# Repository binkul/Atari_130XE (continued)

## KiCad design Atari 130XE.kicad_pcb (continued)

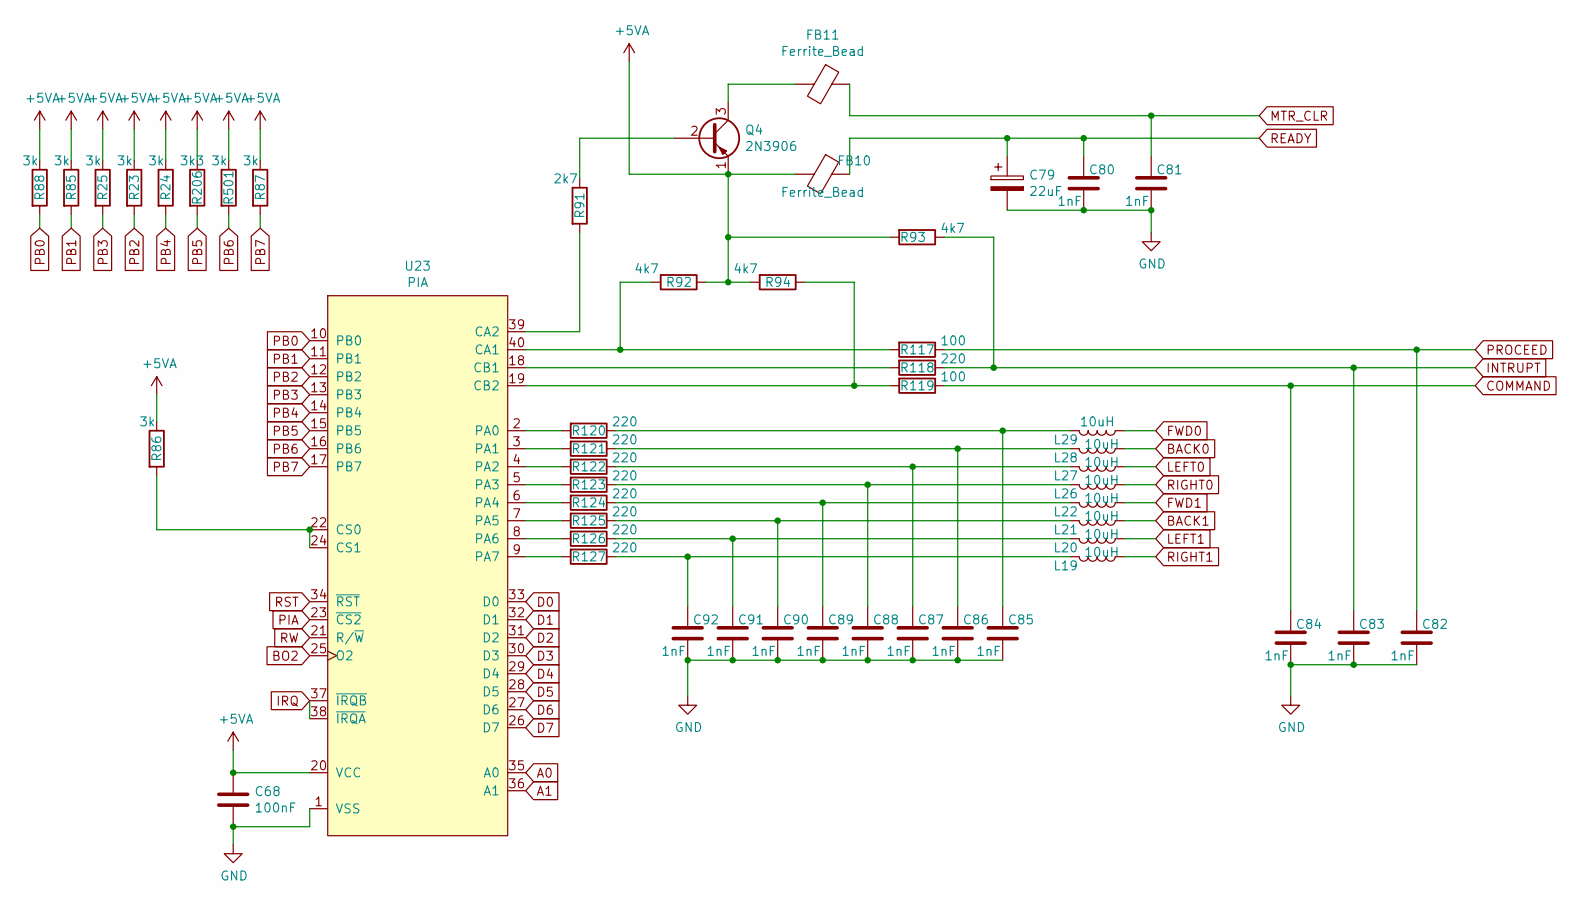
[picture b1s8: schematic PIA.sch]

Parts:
C68: 100nF; C_Axial_L5.1mm_D2.5mm_P12.50mm_Horizontal
C79: 22uF; CP_Axial_L11.0mm_D5.0mm_P18.00mm_Horizontal
C80, C81, C82, C83, C84, C85, C86, C87, C88, C89, C90, C91, C92: 1nF; C_Axial_L5.1mm_D2.5mm_P12.50mm_Horizontal
FB10, FB11: Ferrite_Bead; L_Axial_L7.0mm_D3.3mm_P12.50mm_Horizontal_Fastron_MICC
L19, L20, L21, L22, L26, L27, L28, L29: 10uH; L_Axial_L7.0mm_D3.3mm_P12.50mm_Horizontal_Fastron_MICC
Q4: 2N3906; TO-92_Wide
R23, R24, R25, R85, R86, R87, R88, R501: 3k; R_Axial_DIN0207_L3.6mm_D2.2mm_P10.16mm_Horizontal
R91: 2k7; R_Axial_DIN0207_L3.6mm_D2.2mm_P10.16mm_Horizontal
R92, R93, R94: 4k7; R_Axial_DIN0207_L3.6mm_D2.2mm_P10.16mm_Horizontal
R117, R119: 100; R_Axial_DIN0207_L3.6mm_D2.2mm_P10.16mm_Horizontal
R118, R120, R121, R122, R123, R124, R125, R126, R127: 220; R_Axial_DIN0207_L3.6mm_D2.2mm_P10.16mm_Horizontal
R206: 3k3; R_Axial_DIN0207_L3.6mm_D2.2mm_P10.16mm_Horizontal
U23: PIA; DIP-40_W15.24mm_Socket

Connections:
+5VA: C68.1, FB10.2, Q4.1 (E), R23.1, R24.1, R25.1, R85.1, R86.1, R87.1, R88.1, R92.1, R93.2, R94.2, R206.1, R501.1, U23.20 (VCC); also elsewhere on the board
A0: U23.35 (A0); also elsewhere on the board
A1: U23.36 (A1); also elsewhere on the board
BACK0: L28.1; also elsewhere on the board
BACK1: L21.1; also elsewhere on the board
BO2: U23.25 (O2); also elsewhere on the board
COMMAND: C84.1, R119.1; also elsewhere on the board
D0: U23.33 (D0); also elsewhere on the board
D1: U23.32 (D1); also elsewhere on the board
D2: U23.31 (D2); also elsewhere on the board
D3: U23.30 (D3); also elsewhere on the board
D4: U23.29 (D4); also elsewhere on the board
D5: U23.28 (D5); also elsewhere on the board
D6: U23.27 (D6); also elsewhere on the board
D7: U23.26 (D7); also elsewhere on the board
FWD0: L29.1; also elsewhere on the board
FWD1: L22.1; also elsewhere on the board
GND: C68.2, C79.2, C80.2, C81.2, C82.2, C83.2, C84.2, C85.2, C86.2, C87.2, C88.2, C89.2, C90.2, C91.2, C92.2, U23.1 (VSS); also elsewhere on the board
INTRUPT: C83.1, R93.1, R118.1; also elsewhere on the board
IRQ: U23.37 (~IRQB), U23.38 (~IRQA); also elsewhere on the board
LEFT0: L27.1; also elsewhere on the board
LEFT1: L20.1; also elsewhere on the board
MTR_CLR: C81.1, FB11.1; also elsewhere on the board
unnamed: C85.1, L29.2, R120.1
unnamed: C86.1, L28.2, R121.1
unnamed: C87.1, L27.2, R122.1
unnamed: C88.1, L26.2, R123.1
unnamed: C89.1, L22.2, R124.1
unnamed: C90.1, L21.2, R125.1
unnamed: C91.1, L20.2, R126.1
unnamed: C92.1, L19.2, R127.1
unnamed: FB11.2, Q4.3 (C)
unnamed: Q4.2 (B), R91.1
unnamed: R86.2, U23.22 (CS0), U23.24 (CS1)
unnamed: R91.2, U23.39 (CA2)
unnamed: R92.2, R117.2, U23.40 (CA1)
unnamed: R118.2, U23.18 (CB1)
unnamed: R94.1, R119.2, U23.19 (CB2)
unnamed: R120.2, U23.2 (PA0)
unnamed: R121.2, U23.3 (PA1)
unnamed: R122.2, U23.4 (PA2)
unnamed: R123.2, U23.5 (PA3)
unnamed: R124.2, U23.6 (PA4)
unnamed: R125.2, U23.7 (PA5)
unnamed: R126.2, U23.8 (PA6)
unnamed: R127.2, U23.9 (PA7)
PB0: R88.2, U23.10 (PB0); also elsewhere on the board
PB1: R85.2, U23.11 (PB1); also elsewhere on the board
PB2: R23.2, U23.12 (PB2); also elsewhere on the board
PB3: R25.2, U23.13 (PB3); also elsewhere on the board
PB4: R24.2, U23.14 (PB4); also elsewhere on the board
PB5: R206.2, U23.15 (PB5); also elsewhere on the board
PB6: R501.2, U23.16 (PB6)
PB7: R87.2, U23.17 (PB7); also elsewhere on the board
PIA: U23.23 (~CS2); also elsewhere on the board
PROCEED: C82.1, R117.1; also elsewhere on the board
READY: C79.1, C80.1, FB10.1; also elsewhere on the board
RIGHT0: L26.1; also elsewhere on the board
RIGHT1: L19.1; also elsewhere on the board
RST: U23.34 (~RST); also elsewhere on the board
RW: U23.21 (R/~W); also elsewhere on the board

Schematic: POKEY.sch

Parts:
C62, C71, C72, C73, C74, C75, C76, C77, C78: 1nF; C_Axial_L5.1mm_D2.5mm_P12.50mm_Horizontal
C63, C64, C65, C66: 47nF; C_Axial_L5.1mm_D2.5mm_P12.50mm_Horizontal
C69, C70: 100nF; C_Axial_L5.1mm_D2.5mm_P12.50mm_Horizontal
C98: 10uF; CP_Axial_L11.0mm_D6.0mm_P18.00mm_Horizontal
D5: 1N4148; D_DO-35_SOD27_P12.70mm_Horizontal
J108, J109, J110, J111: pin; PinHeader_1x01_P2.00mm_Vertical
L15, L16, L17, L18: 10uH; L_Axial_L7.0mm_D3.3mm_P12.50mm_Horizontal_Fastron_MICC
R74, R75: 3k; R_Axial_DIN0207_L3.6mm_D2.2mm_P10.16mm_Horizontal
R76, R77, R78, R79: 1k8; R_Axial_DIN0207_L3.6mm_D2.2mm_P10.16mm_Horizontal
R80: 1k; R_Axial_DIN0207_L3.6mm_D2.2mm_P10.16mm_Horizontal
R81, R82, R83, R84: 4k7; R_Axial_DIN0207_L3.6mm_D2.2mm_P10.16mm_Horizontal
R89, R96: 47k; R_Axial_DIN0207_L3.6mm_D2.2mm_P10.16mm_Horizontal
R90, R128, R129, R130, R131: 100; R_Axial_DIN0207_L3.6mm_D2.2mm_P10.16mm_Horizontal
R137: 270; R_Axial_DIN0207_L3.6mm_D2.2mm_P10.16mm_Horizontal
R138, R139, R140, R141, R142, R143, R144, R145, R146, R147, R148, R149, R150, R151, R152, R153: 220; R_Axial_DIN0207_L3.6mm_D2.2mm_P10.16mm_Horizontal
U22: POKEY; DIP-40_W15.24mm_Socket
U24, U25: CD4051B; DIP-16_W7.62mm_Socket
W1: 0; R_Axial_DIN0207_L3.6mm_D2.2mm_P10.16mm_Horizontal

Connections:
+5VA: C69.1, C70.1, D5.1 (K), R74.1, R75.2, R80.2, R81.1, R82.1, R83.1, R84.1, R89.2, R96.2, U24.16 (VDD), U25.16 (VDD); also elsewhere on the board
A0: U22.36 (A0); also elsewhere on the board
A1: U22.35 (A1); also elsewhere on the board
A2: U22.34 (A2); also elsewhere on the board
A3: U22.33 (A3); also elsewhere on the board
BO2: U22.7 (O2); also elsewhere on the board
BSC: R137.1; also elsewhere on the board
CLK_IN: C76.1, R129.1; also elsewhere on the board
CLK_OUT: C75.1, R128.1; also elsewhere on the board
D0: U22.38 (D0); also elsewhere on the board
D1: U22.39 (D1); also elsewhere on the board
D2: U22.40 (D2); also elsewhere on the board
D3: U22.2 (D3); also elsewhere on the board
D4: U22.3 (D4); also elsewhere on the board
D5: U22.4 (D5); also elsewhere on the board
D6: U22.5 (D6); also elsewhere on the board
D7: U22.6 (D7); also elsewhere on the board
DATA_IN: C77.1, R130.1; also elsewhere on the board
DATA_OUT: C78.1, R131.1; also elsewhere on the board
GND: C62.2, C63.2, C64.2, C65.2, C66.2, C69.2, C70.2, C71.2, C72.2, C73.2, C74.2, C75.2, C76.2, C77.2, C78.2, C98.2, J108.1, J109.1, J110.1, J111.1, R90.2, U22.1 (VSS), U22.8 (P6), U22.9 (P7), U22.11 (P5), U24.6 (INH), U24.7 (VEE), U24.8 (VSS), U25.6 (INH), U25.7 (VEE), U25.8 (VSS), W1.2; also elsewhere on the board
IN0: R146.1; also elsewhere on the board
IN1: R147.1; also elsewhere on the board
IN2: R148.1; also elsewhere on the board
IN3: R149.1; also elsewhere on the board
IN4: R150.1; also elsewhere on the board
IN5: R151.1; also elsewhere on the board
IN6: R152.1; also elsewhere on the board
IN7: R153.1; also elsewhere on the board
IRQ: U22.29 (~IRQ); also elsewhere on the board
K0: U22.23 (~K0), U24.11 (A)
K1: U22.22 (~K1), U24.10 (B)
K2: U22.21 (~K2), U24.9 (C)
K3: U22.20 (~K3), U25.11 (A)
K4: U22.19 (~K4), U25.10 (B)
K5: U22.18 (~K5), U25.9 (C)
unnamed: C63.1, R78.2, U22.13 (P3)
unnamed: C64.1, R76.2, U22.15 (P1)
unnamed: C65.1, R77.2, U22.14 (P0)
unnamed: C66.1, R79.2, U22.12 (P2)
unnamed: C71.1, L17.2, R76.1
unnamed: C72.1, L18.2, R77.1
unnamed: C73.1, L15.2, R78.1
unnamed: C74.1, L16.2, R79.1
unnamed: D5.2 (A), R96.1, R137.2, U22.16 (~KR2)
unnamed: R74.2, U22.31 (CS1)
unnamed: R75.1, U22.10 (P4), W1.1
unnamed: R89.1, U22.25 (~KR1), U24.3 (X)
unnamed: R90.1, U25.3 (X)
unnamed: R81.2, R128.2, U22.27 (ACLK)
unnamed: R82.2, R129.2, U22.26 (BCLK)
unnamed: R83.2, R130.2, U22.24 (SID)
unnamed: R84.2, R131.2, U22.28 (SOD)
unnamed: R138.2, U25.4 (X7)
unnamed: R139.2, U25.2 (X6)
unnamed: R140.2, U25.5 (X5)
unnamed: R141.2, U25.1 (X4)
unnamed: R142.2, U25.12 (X3)
unnamed: R143.2, U25.15 (X2)
unnamed: R144.2, U25.14 (X1)
unnamed: R145.2, U25.13 (X0)
unnamed: R146.2, U24.13 (X0)
unnamed: R147.2, U24.14 (X1)
unnamed: R148.2, U24.15 (X2)
unnamed: R149.2, U24.12 (X3)
unnamed: R150.2, U24.1 (X4)
unnamed: R151.2, U24.5 (X5)
unnamed: R152.2, U24.2 (X6)
unnamed: R153.2, U24.4 (X7)
OUT0: R145.1; also elsewhere on the board
OUT1: R144.1; also elsewhere on the board
OUT2: R143.1; also elsewhere on the board
OUT3: R142.1; also elsewhere on the board
OUT4: R141.1; also elsewhere on the board
OUT5: R140.1; also elsewhere on the board
OUT6: R139.1; also elsewhere on the board
OUT7: R138.1; also elsewhere on the board
POKEY: U22.30 (~CS0); also elsewhere on the board
POT_A0: L18.1; also elsewhere on the board
POT_A1: L16.1; also elsewhere on the board
POT_B0: L17.1; also elsewhere on the board
POT_B1: L15.1; also elsewhere on the board
RW: U22.32 (R/~W); also elsewhere on the board
SOUND: R80.1, U22.37 (AUDIO); also elsewhere on the board

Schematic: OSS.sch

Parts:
C28: 100nF; C_Axial_L5.1mm_D2.5mm_P12.50mm_Horizontal
U5: 27C128; DIP-28_W15.24mm_Socket

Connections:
+5VA: C28.1, U5.1 (VPP), U5.27 (~PGM), U5.28 (VCC); also elsewhere on the board
A0: U5.10 (A0); also elsewhere on the board
A1: U5.9 (A1); also elsewhere on the board
A2: U5.8 (A2); also elsewhere on the board
A3: U5.7 (A3); also elsewhere on the board
A4: U5.6 (A4); also elsewhere on the board
A5: U5.5 (A5); also elsewhere on the board
A6: U5.4 (A6); also elsewhere on the board
A7: U5.3 (A7); also elsewhere on the board
A8: U5.25 (A8); also elsewhere on the board
A9: U5.24 (A9); also elsewhere on the board
A10: U5.21 (A10); also elsewhere on the board
A11: U5.23 (A11); also elsewhere on the board
A12: U5.2 (A12); also elsewhere on the board
A13: U5.26 (A13); also elsewhere on the board
D0: U5.11 (D0); also elsewhere on the board
D1: U5.12 (D1); also elsewhere on the board
D2: U5.13 (D2); also elsewhere on the board
D3: U5.15 (D3); also elsewhere on the board
D4: U5.16 (D4); also elsewhere on the board
D5: U5.17 (D5); also elsewhere on the board
D6: U5.18 (D6); also elsewhere on the board
D7: U5.19 (D7); also elsewhere on the board
GND: C28.2, U5.14 (GND); also elsewhere on the board
OS: U5.20 (~CE), U5.22 (~OE); also elsewhere on the board

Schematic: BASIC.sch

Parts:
C27: 100nF; C_Axial_L5.1mm_D2.5mm_P12.50mm_Horizontal
U4: BASIC_ROM; DIP-24_W15.24mm_Socket

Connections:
+5VA: C27.1, U4.24 (VCC); also elsewhere on the board
A0: U4.8 (A0); also elsewhere on the board
A1: U4.7 (A1); also elsewhere on the board
A2: U4.6 (A2); also elsewhere on the board
A3: U4.5 (A3); also elsewhere on the board
A4: U4.4 (A4); also elsewhere on the board
A5: U4.3 (A5); also elsewhere on the board
A6: U4.2 (A6); also elsewhere on the board
A7: U4.1 (A7); also elsewhere on the board
A8: U4.23 (A8); also elsewhere on the board
A9: U4.22 (A9); also elsewhere on the board
A10: U4.19 (A10); also elsewhere on the board
A11: U4.18 (A11); also elsewhere on the board
A12: U4.21 (A12); also elsewhere on the board
BASIC: U4.20 (~CS); also elsewhere on the board
D0: U4.9 (D0); also elsewhere on the board
D1: U4.10 (D1); also elsewhere on the board
D2: U4.11 (D2); also elsewhere on the board
D3: U4.13 (D3); also elsewhere on the board
D4: U4.14 (D4); also elsewhere on the board
D5: U4.15 (D5); also elsewhere on the board
D6: U4.16 (D6); also elsewhere on the board
D7: U4.17 (D7); also elsewhere on the board
GND: C27.2, U4.12 (GND); also elsewhere on the board

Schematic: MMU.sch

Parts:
C26: 100nF; C_Axial_L5.1mm_D2.5mm_P12.50mm_Horizontal
R12, R15: 3k; R_Axial_DIN0207_L3.6mm_D2.2mm_P10.16mm_Horizontal
R13, R14: 1k; R_Axial_DIN0207_L3.6mm_D2.2mm_P10.16mm_Horizontal
U2: 74LS138; DIP-16_W7.62mm_Socket
U3: MMU; DIP-20_W7.62mm_Socket
U18: 74LS08; DIP-14_W7.62mm_Socket

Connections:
+5VA: C26.1, R12.1, R15.1, U2.16 (VCC), U3.20 (VCC); also elsewhere on the board
A8: U2.1 (A0); also elsewhere on the board
A9: U2.2 (A1); also elsewhere on the board
A10: U2.3 (A2); also elsewhere on the board
A11: U3.1 (A11); also elsewhere on the board
A12: U3.2 (A12); also elsewhere on the board
A13: U3.3 (A13); also elsewhere on the board
A14: U3.4 (A14); also elsewhere on the board
A15: U3.5 (A15); also elsewhere on the board
BASIC: U3.13 (~BASIC); also elsewhere on the board
CASINH: U3.16 (~CI); also elsewhere on the board
CCTL: U2.10 (O5); also elsewhere on the board
D1XX: U2.14 (O1); also elsewhere on the board
D6XX: U2.9 (O6); also elsewhere on the board
D7XX: U2.7 (O7); also elsewhere on the board
E3: R12.2, U2.6 (E3)
GND: C26.2, R13.2, R14.2, U2.5 (E2), U2.8 (GND), U3.10 (VSS); also elsewhere on the board
GTIA: U18.8; also elsewhere on the board
MPD: R15.2, U3.14 (~MPD); also elsewhere on the board
unnamed: U2.4 (E1), U3.17 (~IO)
unnamed: U2.15 (O0), U18.9, U18.10
OS: U3.15 (~OS); also elsewhere on the board
PB0: U3.9 (REN); also elsewhere on the board
PB1: U3.18 (~BE); also elsewhere on the board
PB7: U3.6 (~MAP); also elsewhere on the board
PIA: U2.12 (O3); also elsewhere on the board
POKEY: U2.13 (O2); also elsewhere on the board
RD4: R14.1, U3.7 (RD4); also elsewhere on the board
RD5: R13.1, U3.8 (RD5); also elsewhere on the board
REF: U3.11 (~REF); also elsewhere on the board
S4: U3.19 (~S4); also elsewhere on the board
S5: U3.12 (~S5); also elsewhere on the board

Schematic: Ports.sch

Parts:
C93: 100nF; C_Axial_L5.1mm_D2.5mm_P12.50mm_Horizontal
C95: 10nF; C_Axial_L5.1mm_D2.5mm_P12.50mm_Horizontal
C102: 1nF; C_Axial_L5.1mm_D2.5mm_P12.50mm_Horizontal
FB12, FB102: Ferrite_Bead; L_Axial_L7.0mm_D3.3mm_P12.50mm_Horizontal_Fastron_MICC
J1: SIO; SIO_Slot
J5, J6: Joystick_Port; Joystick_Pport
J8: Keyboard; PinHeader_1x24_P2.54mm_Vertical
R95: 1k; R_Axial_DIN0207_L3.6mm_D2.2mm_P10.16mm_Horizontal

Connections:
+5VA: C93.1, FB12.2, J8.1, R95.2; also elsewhere on the board
BACK0: J6.2 (Back); also elsewhere on the board
BACK1: J5.2 (Back); also elsewhere on the board
BSC: J8.20; also elsewhere on the board
CLK_IN: J1.1 (CLK_IN); also elsewhere on the board
CLK_OUT: J1.2 (CLK_OUT); also elsewhere on the board
COMMAND: J1.7 (Command); also elsewhere on the board
DATA_IN: J1.3 (Data_In); also elsewhere on the board
DATA_OUT: J1.5 (Data_Out); also elsewhere on the board
FWD0: J6.1 (FWD); also elsewhere on the board
FWD1: J5.1 (FWD); also elsewhere on the board
GND: C93.2, C95.2, C102.2, J1.4 (GND), J1.6 (GND), J5.8 (GND), J6.8 (GND), J8.3; also elsewhere on the board
IN0: J8.17; also elsewhere on the board
IN1: J8.11; also elsewhere on the board
IN2: J8.8; also elsewhere on the board
IN3: J8.16; also elsewhere on the board
IN4: J8.19; also elsewhere on the board
IN5: J8.10; also elsewhere on the board
IN6: J8.4; also elsewhere on the board
IN7: J8.9; also elsewhere on the board
INTRUPT: J1.13 (Intrupt); also elsewhere on the board
LEFT0: J6.3 (Left); also elsewhere on the board
LEFT1: J5.3 (Left); also elsewhere on the board
MTR_CLR: J1.8 (Mtr_Ctrl); also elsewhere on the board
unnamed: C95.1, J8.2, R95.1
OPTION: J8.23; also elsewhere on the board
OUT0: J8.18; also elsewhere on the board
OUT1: J8.13; also elsewhere on the board
OUT2: J8.15; also elsewhere on the board
OUT3: J8.5; also elsewhere on the board
OUT4: J8.14; also elsewhere on the board
OUT5: J8.6; also elsewhere on the board
OUT6: J8.12; also elsewhere on the board
OUT7: J8.7; also elsewhere on the board
POT_A0: J6.9 (Pot_A); also elsewhere on the board
POT_A1: J5.9 (Pot_A); also elsewhere on the board
POT_B0: J6.5 (Pot_B); also elsewhere on the board
POT_B1: J5.5 (Pot_B); also elsewhere on the board
PROCEED: J1.9 (Proceed); also elsewhere on the board
READY: J1.10 (VCC); also elsewhere on the board
RESET: J8.24; also elsewhere on the board
RIGHT0: J6.4 (Right); also elsewhere on the board
RIGHT1: J5.4 (Right); also elsewhere on the board
SELECT: J8.22; also elsewhere on the board
SIOAUDIO: J1.11 (SIO_Audio); also elsewhere on the board
START: J8.21; also elsewhere on the board
TRIG0: J6.6 (Trig); also elsewhere on the board
TRIG1: J5.6 (Trig); also elsewhere on the board

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
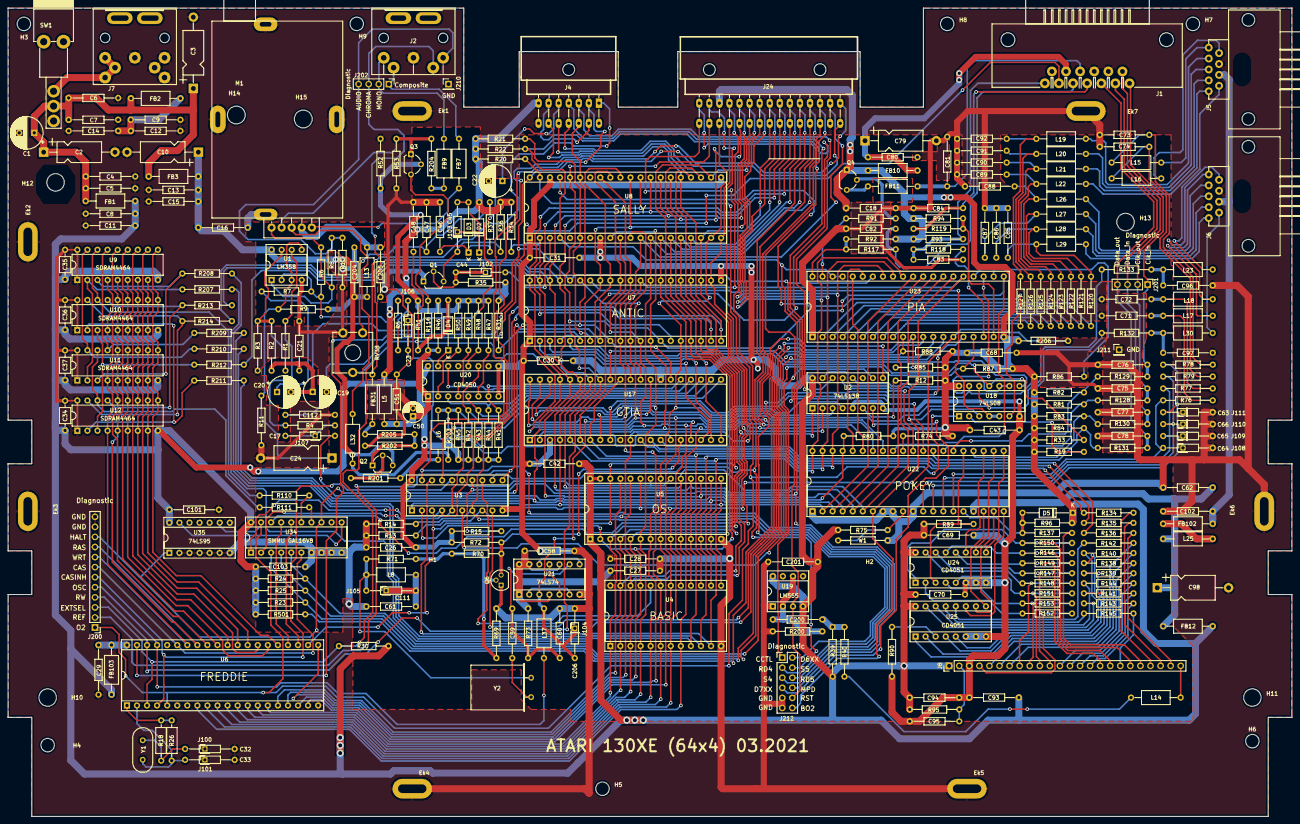
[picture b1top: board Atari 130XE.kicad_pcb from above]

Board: 2 copper layers, 324.0 x 204.0 mm, 344 parts (0 on the bottom side), 285 nets.

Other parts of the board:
C34, C35, C36, C37: 100nF; C_Axial_L3.8mm_D2.6mm_P7.50mm_Horizontal
C94: 10nF; C_Axial_L5.1mm_D2.5mm_P12.50mm_Horizontal
C101, C103: 100nF; C_Axial_L5.1mm_D2.5mm_P12.50mm_Horizontal
J201: Diagnostic; PinHeader_1x04_P2.54mm_Vertical
J210, J211: Diag; PinHeader_1x01_P2.54mm_Vertical
L25: 10uH; L_Axial_L7.0mm_D3.3mm_P12.50mm_Horizontal_Fastron_MICC
R110, R111, R207, R208, R209, R210, R211, R212, R213, R214: 33; R_Axial_DIN0207_L3.6mm_D2.2mm_P10.16mm_Horizontal
U9, U10, U11, U12: DRAM_4464; DIP-18_W7.62mm
U34: MMMU_GAL; DIP-20_W7.62mm_Socket
U35: 74LS95; DIP-14_W7.62mm_Socket

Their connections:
+5VA: C34.1, C35.1, C36.1, C37.1, C94.1, C101.1, C103.1, U9.9, U10.9, U11.9, U12.9, U34.20, U35.14; also elsewhere on the board
A14: U34.1; also elsewhere on the board
A15: U34.2; also elsewhere on the board
CAS: U34.6; also elsewhere on the board
CASBNK: R111.1, U11.16, U12.16
CASMAN: R110.1, U9.16, U10.16
CLK_IN: J201.1; also elsewhere on the board
CLK_OUT: J201.2; also elsewhere on the board
D0: R207.2; also elsewhere on the board
D1: R208.2; also elsewhere on the board
D2: R209.2; also elsewhere on the board
D3: R210.2; also elsewhere on the board
D4: R211.2; also elsewhere on the board
D5: R212.2; also elsewhere on the board
D6: R213.2; also elsewhere on the board
D7: R214.2; also elsewhere on the board
DATA_IN: J201.3; also elsewhere on the board
DATA_OUT: J201.4; also elsewhere on the board
DQ0: R207.1, U9.2, U11.2
DQ1: R208.1, U9.3, U11.3
DQ2: R209.1, U9.15, U11.15
DQ3: R210.1, U9.17, U11.17
DQ4: R211.1, U10.2, U12.2
DQ5: R212.1, U10.3, U12.3
DQ6: R213.1, U10.15, U12.15
DQ7: R214.1, U10.17, U12.17
FA14: U34.16; also elsewhere on the board
FA15: U34.17; also elsewhere on the board
GND: C34.2, C35.2, C36.2, C37.2, C94.2, C101.2, C103.2, J210.1, J211.1, U9.1, U9.18, U10.1, U10.18, U11.1, U11.18, U12.1, U12.18, U34.7, U34.8, U34.9, U34.10, U35.2, U35.3, U35.4, U35.5, U35.6, U35.7, U35.8; also elsewhere on the board
HALT: U34.13, U35.1; also elsewhere on the board
unnamed: R110.2, U34.15
unnamed: R111.2, U34.14
unnamed: U34.11, U35.13
O2: U34.19, U35.9; also elsewhere on the board
PB2: U34.3; also elsewhere on the board
PB3: U34.4; also elsewhere on the board
PB4: U34.5; also elsewhere on the board
PB5: U34.18; also elsewhere on the board
RA0: U9.14, U10.14, U11.14, U12.14; also elsewhere on the board
RA1: U9.13, U10.13, U11.13, U12.13; also elsewhere on the board
RA2: U9.12, U10.12, U11.12, U12.12; also elsewhere on the board
RA3: U9.11, U10.11, U11.11, U12.11; also elsewhere on the board
RA4: U9.8, U10.8, U11.8, U12.8; also elsewhere on the board
RA5: U9.7, U10.7, U11.7, U12.7; also elsewhere on the board
RA6: U9.6, U10.6, U11.6, U12.6; also elsewhere on the board
RA7: U9.10, U10.10, U11.10, U12.10; also elsewhere on the board
RAS: U9.5, U10.5, U11.5, U12.5; also elsewhere on the board
WRT: U9.4, U10.4, U11.4, U12.4; also elsewhere on the board

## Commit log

2021-02-10 Memory and Freddie
2021-02-11 GTIA
2021-02-11 GTIA put on board
2021-02-12 MMU, Joy, Cart and Video
2021-02-14 Put elements on board
2021-02-14 PIA and POKEY
2021-02-15 Pokey finish
2021-02-15 Schema finished
2021-02-16 Audio
2021-02-16 Audio put on board
2021-02-17 Patching
2021-02-18 tracking
2021-02-28 Gerber and Tracking
2021-03-04 Trackimg
2021-03-05 Diagnostic
2021-03-07 Diagnostic pin
2021-03-11 Atari ITX schema
2021-03-19 Add 74LS95
2021-04-22 Error remove
